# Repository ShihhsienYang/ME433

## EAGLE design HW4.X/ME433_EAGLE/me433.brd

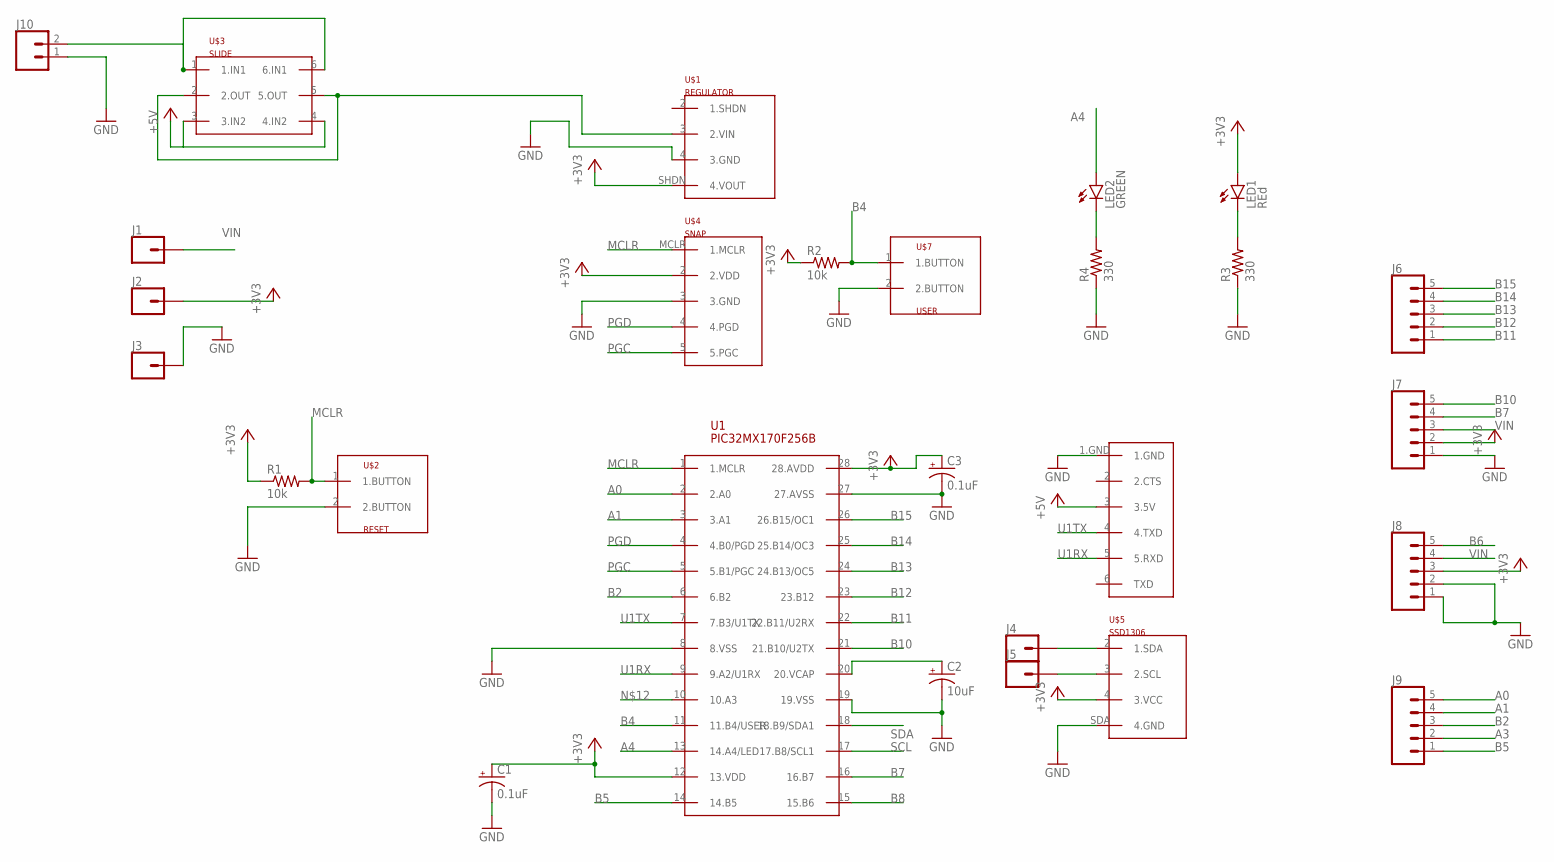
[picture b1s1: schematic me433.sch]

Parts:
C1, C3: 0.1uF; B45181B
C2: 10uF; B45181B
J1, J2, J3, J4, J5: CONN_01PTH_NO_SILK_YES_STOP; 1X01_NO_SILK
J6, J7, J8, J9: CONN_05NO_SILK; 1X05_NO_SILK
J10: CONN_02; 1X02
LED1: REd; LED3MM
LED2: GREEN; LED3MM
R1, R2: 10k; 0204/7
R3, R4: 330; 0204/7
U1: PIC32MX170F256B; DIL28-3
U$1: REGULATOR
U$2: RESET
U$3: SLIDE
U$4: SNAP
U$5: SSD1306
U$6: USBTOUART
U$7: USER

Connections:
+3V3: C1.+, C3.+, J2.1, J7.2, J8.3, LED1.A, R1.1, R2.1, U1.12 (13.VDD), U1.28 (28.AVDD), U$1.SHDN (4.VOUT), U$4.2 (2.VDD), U$5.4 (3.VCC)
+5V: U$6.3 (3.5V)
A0: J9.5, U1.2 (2.A0)
A1: J9.4, U1.3 (3.A1)
A3: J9.2
A4: LED2.A, U1.13 (14.A4/LED)
B2: J9.3, U1.6 (6.B2)
B4: R2.2, U1.11 (11.B4/USER), U$7.1 (1.BUTTON)
B5: J9.1, U1.14 (14.B5)
B6: J8.5
B7: J7.4, U1.16 (16.B7)
B8: U1.15 (15.B6)
B10: J7.5, U1.21 (21.B10/U2TX)
B11: J6.1, U1.22 (22.B11/U2RX)
B12: J6.2, U1.23 (23.B12)
B13: J6.3, U1.24 (24.B13/OC5)
B14: J6.4, U1.25 (25.B14/OC3)
B15: J6.5, U1.26 (26.B15/OC1)
GND: C1.-, C2.-, C3.-, J3.1, J7.1, J8.1, J8.2, J10.1, R3.1, R4.1, U1.8 (8.VSS), U1.19 (19.VSS), U1.27 (27.AVSS), U$1.4 (3.GND), U$2.2 (2.BUTTON), U$4.3 (3.GND), U$5.SDA (4.GND), U$6.1.GND, U$7.2 (2.BUTTON)
MCLR: R1.2, U1.1 (1.MCLR), U$2.1 (1.BUTTON), U$4.MCLR (1.MCLR)
unnamed: J10.2, U$3.1 (1.IN1), U$3.6 (6.IN1)
unnamed: LED1.K (C), R3.2
unnamed: U$3.3 (3.IN2), U$3.4 (4.IN2)
unnamed: U$1.3 (2.VIN), U$3.2 (2.OUT), U$3.5 (5.OUT)
unnamed: LED2.K (C), R4.2
unnamed: J4.1, U$5.2 (1.SDA)
unnamed: J5.1, U$5.3 (2.SCL)
unnamed: C2.+, U1.20 (20.VCAP)
PGC: U1.5 (5.B1/PGC), U$4.5 (5.PGC)
PGD: U1.4 (4.B0/PGD), U$4.4 (4.PGD)
SCL: U1.17 (17.B8/SCL1)
SDA: U1.18 (18.B9/SDA1)
U1RX: U1.9 (9.A2/U1RX), U$6.5 (5.RXD)
U1TX: U1.7 (7.B3/U1TX), U$6.4 (4.TXD)
VIN: J1.1, J7.3, J8.4

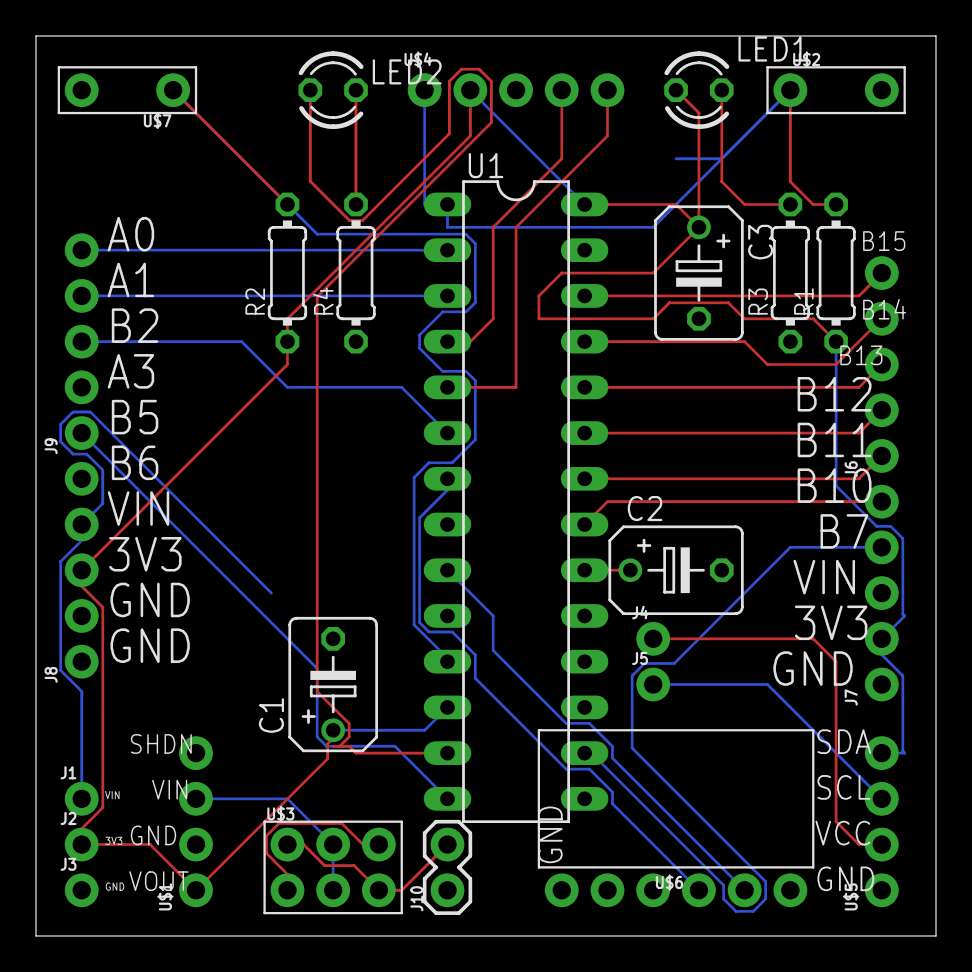
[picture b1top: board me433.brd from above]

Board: 2 copper layers, 50.0 x 50.0 mm, 27 parts (0 on the bottom side), 29 nets.

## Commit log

2022-04-04 04040
2022-04-04 04041
2022-04-04 04042
2022-04-05 04050
2022-04-06 HW2/HW3
2022-04-06 HW2/Images
2022-04-06 HW2/image
2022-04-06 HW2/video
2022-04-14 04/14
2022-04-21 04/20
2022-04-26 0426
2022-04-28 0427
2022-04-29 0428
2022-05-10 05/10
2022-05-10 05/11
2022-06-08 06/07
2022-06-12 06/12
